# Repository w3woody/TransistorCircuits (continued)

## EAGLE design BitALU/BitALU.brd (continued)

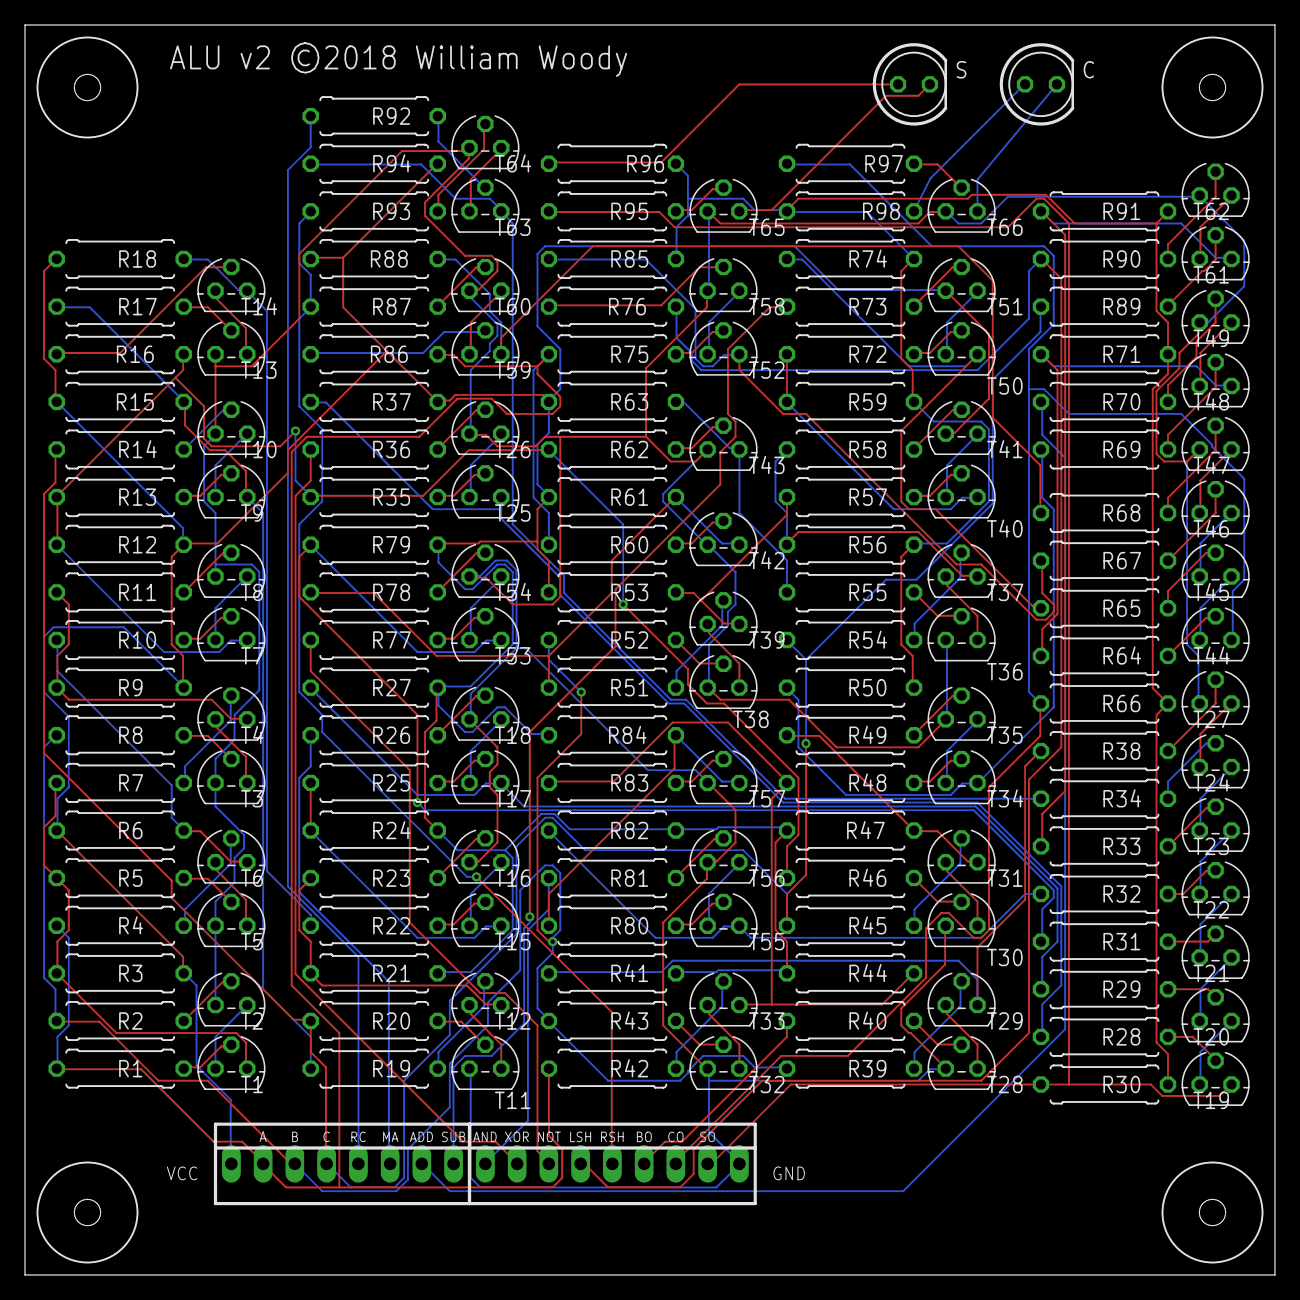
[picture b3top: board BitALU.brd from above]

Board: 2 copper layers, 100.0 x 100.0 mm, 168 parts (0 on the bottom side), 149 nets.

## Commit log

2018-12-16 Initial check-in of BitALU circuit
2018-12-16 Add accumulator, register.
2018-12-22 Fix contents of readme files
2019-01-01 New Boards
    Flags control board for A/F/ALU circuits.
    Up/Down counter for SP register.
    U counter for PC/MPC register.
